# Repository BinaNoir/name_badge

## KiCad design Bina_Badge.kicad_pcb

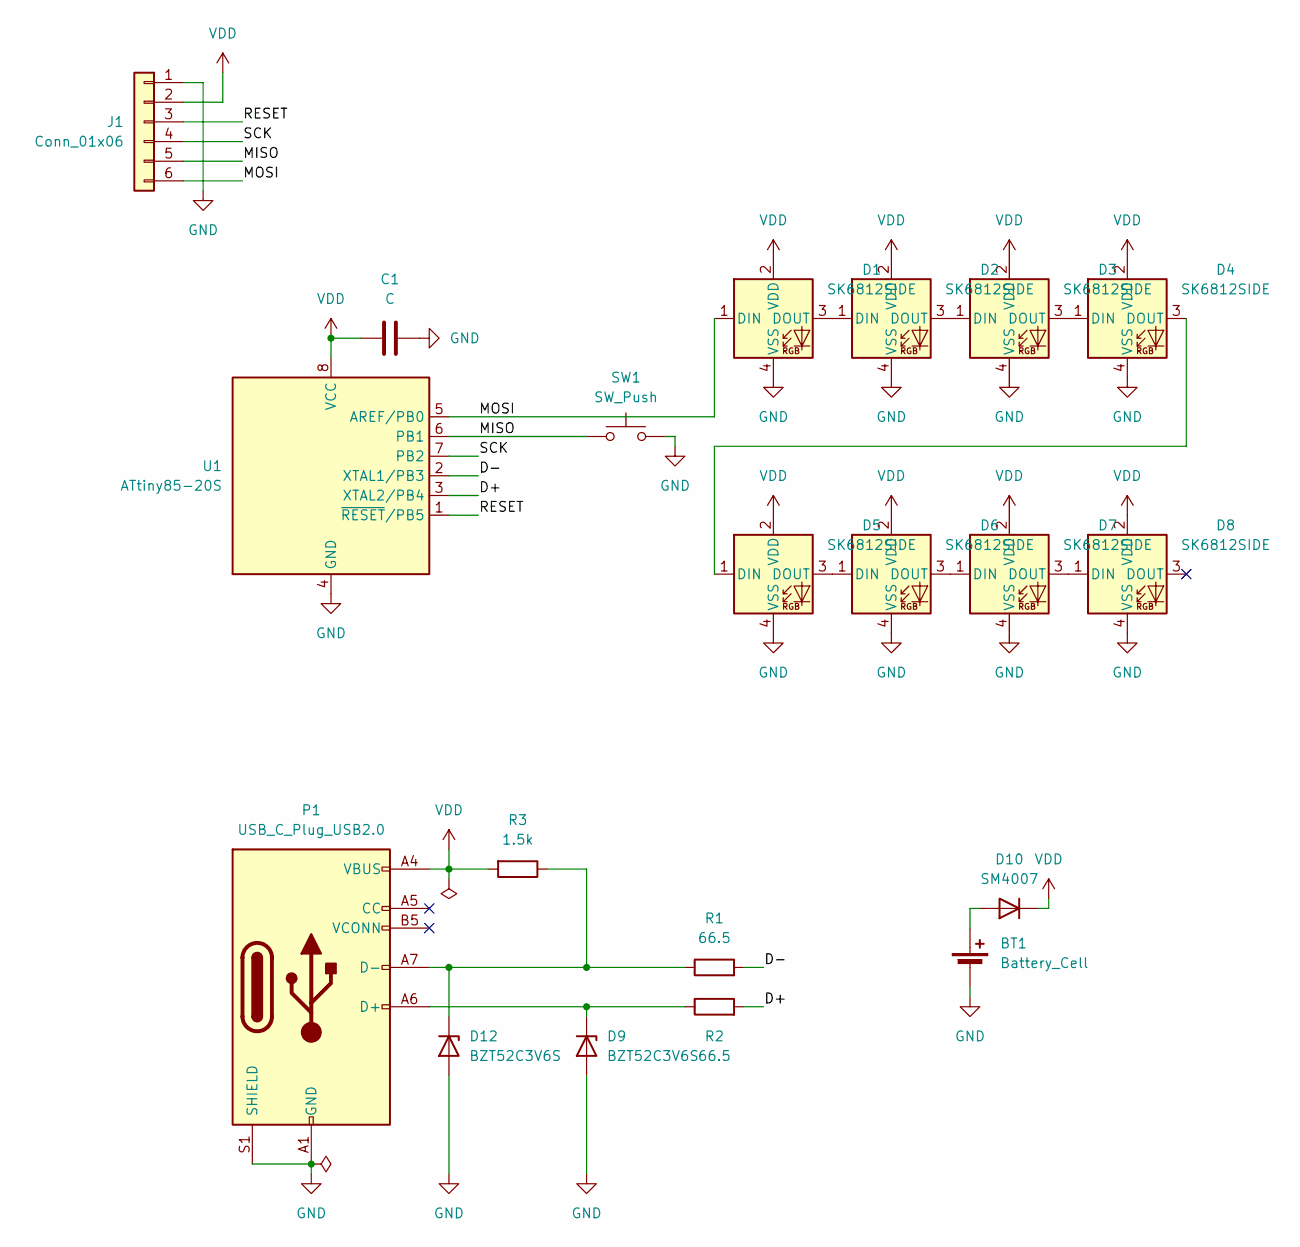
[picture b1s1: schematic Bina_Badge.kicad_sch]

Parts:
BT1: Battery_Cell; BatteryHolder_Multicomp_BC-2001_1x2032
C1: C; C_0805_2012Metric
D1, D2, D3, D4, D5, D6, D7, D8: SK6812SIDE; LED-SMD_4P-L4.0-W1.6-L
D9, D12: BZT52C3V6S; D_SOD-123F
D10: SM4007; D_MELF
J1: Conn_01x06; PinHeader_1x06_P2.54mm_Vertical
P1: USB_C_Plug_USB2.0; USB_C_Receptacle_HRO_TYPE-C-31-M-12
R1, R2: 66.5; R_0805_2012Metric
R3: 1.5k; R_0805_2012Metric
SW1: SW_Push; Panasonic_EVQPUJ_EVQPUA; JLCPCB C589215
U1: ATtiny85-20S; SOIC-8W_5.3x5.3mm_P1.27mm

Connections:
/D+: R2.2, U1.3 (XTAL2/PB4)
/D-: R1.2, U1.2 (XTAL1/PB3)
/MISO: J1.5, SW1.2, U1.6 (PB1)
/MOSI: D1.1 (DIN), J1.6, U1.5 (AREF/PB0)
/RESET: J1.3, U1.1 (~RESET/PB5)
/SCK: J1.4, U1.7 (PB2)
GND: BT1.2 (-), C1.2, D1.4 (VSS), D2.4 (VSS), D3.4 (VSS), D4.4 (VSS), D5.4 (VSS), D6.4 (VSS), D7.4 (VSS), D8.4 (VSS), D9.2 (A), D12.2 (A), J1.1, P1.A1 (GND), P1.A12 (GND), P1.B1 (GND), P1.B12 (GND), P1.S1 (SHIELD), SW1.1, U1.4 (GND)
unnamed: BT1.1 (+), D10.2 (A)
unnamed: D1.3 (DOUT), D2.1 (DIN)
unnamed: D2.3 (DOUT), D3.1 (DIN)
unnamed: D3.3 (DOUT), D4.1 (DIN)
unnamed: D4.3 (DOUT), D5.1 (DIN)
unnamed: D5.3 (DOUT), D6.1 (DIN)
unnamed: D6.3 (DOUT), D7.1 (DIN)
unnamed: D7.3 (DOUT), D8.1 (DIN)
unnamed: D9.1 (K), P1.A6 (D+), R2.1
unnamed: D12.1 (K), P1.A7 (D-), R1.1, R3.1
VDD: C1.1, D1.2 (VDD), D2.2 (VDD), D3.2 (VDD), D4.2 (VDD), D5.2 (VDD), D6.2 (VDD), D7.2 (VDD), D8.2 (VDD), D10.1 (K), J1.2, P1.A4 (VBUS), P1.A9 (VBUS), P1.B4 (VBUS), P1.B9 (VBUS), R3.2, U1.8 (VCC)

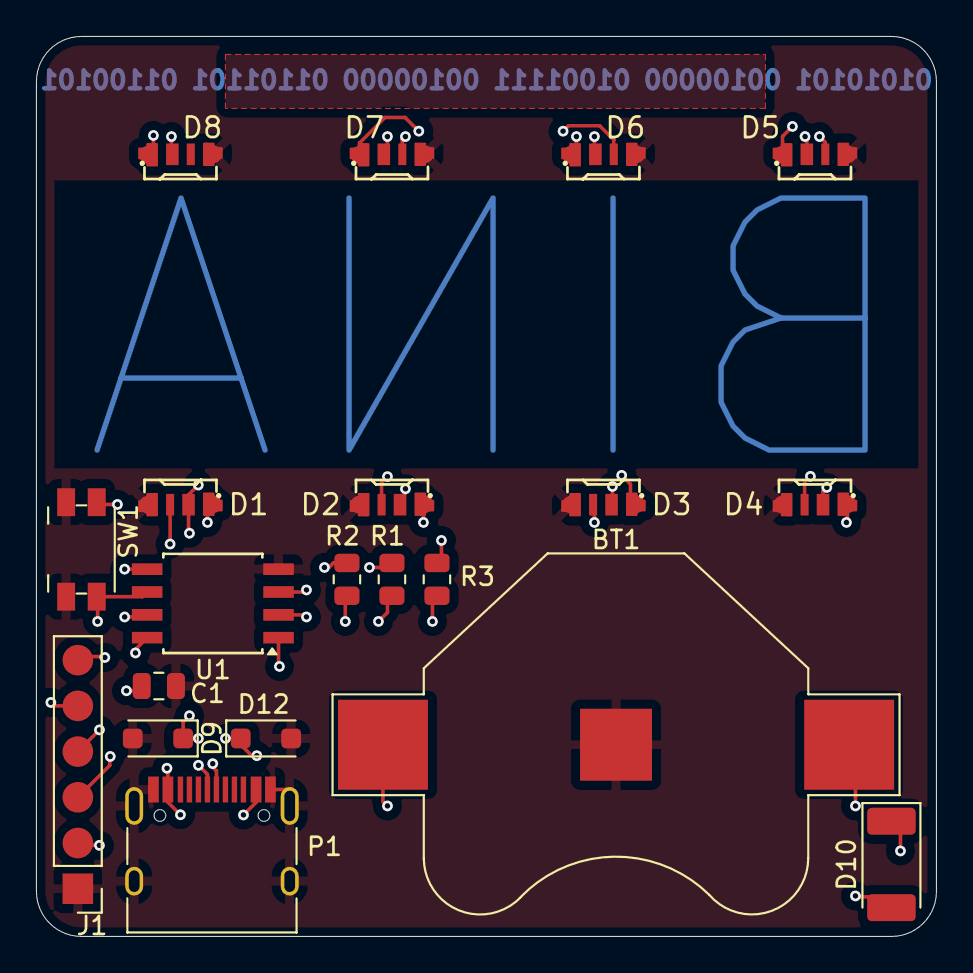
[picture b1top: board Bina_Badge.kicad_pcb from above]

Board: 2 copper layers, 50.0 x 50.0 mm, 20 parts (0 on the bottom side), 18 nets.

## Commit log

2025-11-16 wip kicad files
2025-11-23 production ready
